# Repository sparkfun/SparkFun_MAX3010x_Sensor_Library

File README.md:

SparkFun MAX301x Particle Sensor Library
===========================================================

[*SparkFun Reflectance, Particle, and Pulse Ox sensor - MAX30105 (SEN-14045)*](https://www.sparkfun.com/products/14045)

That's my heartbeat!

This is a breadboard friendly breakout board for the Maxim MAX30105 reflectance, particle, and pulse ox sensor.

This library should work with other MAX3010x sensors including the MAX30102, MAX30101, and MAX30100. 

Library written by Nathan Seidle ([SparkFun](http://www.sparkfun.com)) and Peter Jansen ([Open Sensing Lab](https://github.com/opensensinglab)).

Repository Contents
-------------------

* **/examples** - Example sketches for the library (.ino). Run these from the Arduino IDE. 
* **/src** - Source files for the library (.cpp, .h).
* **keywords.txt** - Keywords from this library that will be highlighted in the Arduino IDE. 
* **library.properties** - General library properties for the Arduino package manager. 

Documentation
--------------

* **[Installing an Arduino Library Guide](https://learn.sparkfun.com/tutorials/installing-an-arduino-library)** - Basic information on how to install an Arduino library.
* **[Product Repository (MAX30105)](https://github.com/sparkfun/MAX30105_Particle_Sensor_Breakout)** - Main repository (including hardware files) for the MAX30105 particle sensor breakout board.
* **[Product Repository (MAX30101)](https://github.com/sparkfun/SparkFun_Photodetector_Breakout_MAX30101_Qwiic)** - Main repository (including hardware files) for the SparkFun Photodetector (MAX30101) - Qwiic.
* **[Hookup Guide (MAX30105)](https://learn.sparkfun.com/tutorials/max30105-particle-and-pulse-ox-sensor-hookup-guide)** - Basic hookup guide for the MAX30105 Particle Sensor breakout board.
* **[Hookup Guide (MAX30101)](https://learn.sparkfun.com/tutorials/sparkfun-photodetector-max30101-hookup-guide)** - Basic hookup guide for the SparkFun Photodetector (MAX30101) - Qwiic.

License Information
-------------------

This product is _**open source**_! 

Various bits of the code have different licenses applied. Anything SparkFun wrote is beerware; if you see me (or any other SparkFun employee) at the local, and you've found our code helpful, please buy us a round! Anything Maxim wrote has its own license. Anything that was co-writing with Peter Jansen is BSD.

Please use, reuse, and modify these files as you see fit. Please maintain attribution to SparkFun Electronics and release anything derivative under the same license.

Distributed as-is; no warranty is given.

- Your friends at SparkFun.

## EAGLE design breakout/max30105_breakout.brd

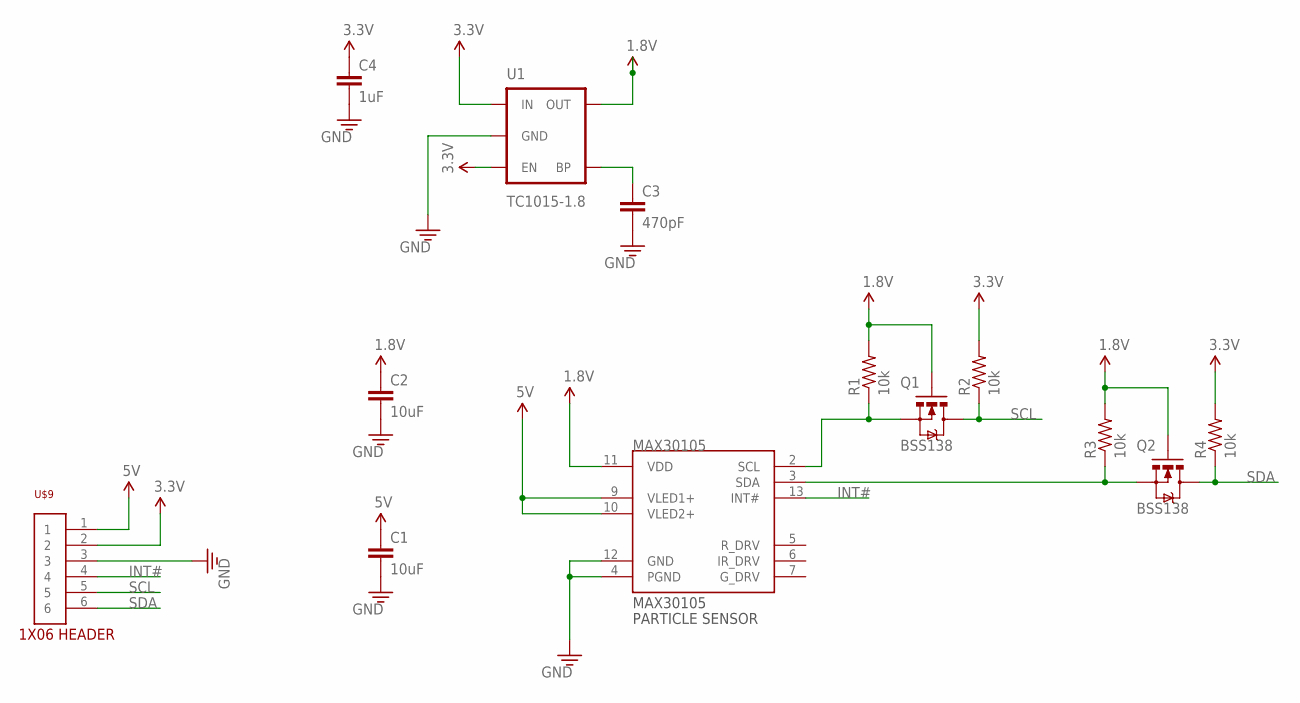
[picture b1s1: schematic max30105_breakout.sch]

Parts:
C1, C2: 10uF; 0805
C3: 470pF; 0603
C4: 1uF; 0603
MAX30105: MAX30105
Q1, Q2: BSS138; SOT23
R1, R2, R3, R4: 10k; 0603
U1: TC1015-1.8; SOT23-5
U$9: 1X06

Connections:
1.8V: C2.1, MAX30105.11 (VDD), Q1.1 (G), Q2.1 (G), R1.2, R3.2, U1.5 (OUT)
3.3V: C4.1, R2.2, R4.2, U1.1 (IN), U1.3 (EN), U$9.2
5V: C1.1, MAX30105.9 (VLED1+), MAX30105.10 (VLED2+), U$9.1
GND: C1.2, C2.2, C3.2, C4.2, MAX30105.4 (PGND), MAX30105.12 (GND), U1.2 (GND), U$9.3
INT#: MAX30105.13 (INT#), U$9.4
unnamed: MAX30105.2 (SCL), Q1.2 (S), R1.1
unnamed: C3.1, U1.4 (BP)
unnamed: MAX30105.3 (SDA), Q2.2 (S), R3.1
SCL: Q1.3 (D), R2.1, U$9.5
SDA: Q2.3 (D), R4.1, U$9.6

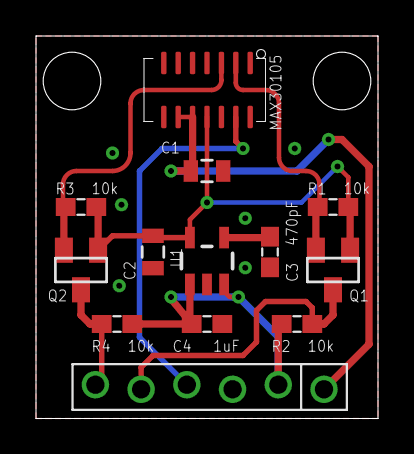
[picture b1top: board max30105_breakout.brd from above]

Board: 2 copper layers, 19.0 x 21.2 mm, 13 parts (0 on the bottom side), 10 nets.

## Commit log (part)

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2016-09-18 added breakout board schematics, board files, and renders
2016-09-18 Creating driver scaffold
2016-09-18 More scaffold -- added initial check for partID/revisionID
2016-09-18 Added die temperature reading
2016-09-18 Most of the basic configuration registers have been added, with the exception of the multiled configuration, and FIFO configuration. Data collection/FIFO reading is still TODO
2016-09-18 Added picture of breakout board
2016-09-22 Corrected register change bug. Added bit polling. Added tempF.
    All these are fairly small changes.
2016-09-22 Adding function to enable slots
2016-09-22 Implemented bitMask technique
    Simplified a bunch of functions.
2016-09-22 Added readData function
2016-09-23 Move config to library as 'defaultSetup'. Added FIFO WR/RW pointer checking.
    No major changes, just simplifcations and clean ups.
2016-09-23 Creating circular buffer for continual reading
    Works well. This is a really sensitive IC!
2016-09-23 Added 400kHz support. Defaults to 100kHz. Added Hz output.
2016-09-23 Added interrupt support
2016-09-23 Added proximity mode interrupt threshold
2016-09-24 Genericize to work with any I2C port, not just Wire.
    Needed for platforms like SAMDxx that have multiple I2C ports.
2016-09-25 Default to Wire if no port is provided.
2016-09-27 Fixed bug in SLOT defs. Reworked begin() to fit Arduino guide.
    Does not compile but there's too many things changing. Need to commit
    what's here.
2016-09-27 Moved data reading into library.
2016-09-28 Making ledMode control slot enabling
2016-10-03 Added example sketches. Moved files to match library structure.
2016-10-05 Small changes to heartrate example
2016-10-19 :tada: Added .gitattributes & .gitignore files
2016-10-20 Added adc control to setup(). Added PBA heart rate algorithm.
2016-10-20 Correcting typo
2016-10-20 Adding spo2 SPK algorithm and examples
2016-10-20 Adding heart beat example
2016-10-20 Small typo and white space fixes.
2016-11-16 Adding 3.3V note
2016-11-17 Fixing heartRate code to work on ESP
2016-11-17 Moved register defines to cpp. Changed to const static.
    Const static allows compiler to check for type conflicts.
2016-11-21 Splitting getRed() from getFIFORed() for better examples. When you call getRed() you now get the immediate environmental reading.
2016-11-21 Re-arranging examples
2016-11-21 Adding image to readme
2016-11-29 Rearrange examples
2016-11-30 Fixing directory structure
2016-11-30 Readme fix
2017-01-23 Adding support for SAM21 and other platforms
2017-01-27 Modifying Ex8 to work with SAMD21
2017-01-27 Updating version number
2017-09-03 Use correct separator in keywords.txt
    The Arduino IDE requires the use of a tab separator between the name and identifier. Without this tab the keyword is not highlighted.
    Reference: https://github.com/arduino/Arduino/wiki/Arduino-IDE-1.5:-Library-specification#keywords
2018-02-15 Fixing issue 4
2018-02-15 Rolling library version
2018-02-15 Capitalized Arduino.h. Fix issue 2 on breakout. Remove unused vars. Removed dup defines.
2018-02-15 Rolling lib ver
2018-03-03 Renamed FS to FreqS because there is an overlap with the FS library. Uncommented one line because it seems you had forgotten to do so.
2018-03-28 Fix for issue #12
2018-03-28 Rolling lib version
2018-04-03 Fix issue 14 - change sampleRate to int in example
2018-04-09 Adding example to demo 3200Hz reading for issue #2
2018-04-10 Roll lib ver
2018-06-08 Fix error in operator precedence
2018-06-08 Lib ver roll
2018-12-17 Sensor values mix up when using multiple sensors
    When using 2 (or more) sensors on the same device the sensor values read from the sensors can get mixed up.
    The struct sense is defined as a global and is reused from multiple instances of the MAX30105 class.
    Solution:
    Declare sense as class private:
2019-01-24 Change how we readTemperature(). Updated Temp Sense example.
    Fix for issue 19.
2019-12-27 Changed Begin function to prevent call to wire->begin (#1)
2019-12-27 changed library properties
2019-12-30 Changed Library properties. Added example to run MAX on EmotiBit.
2020-01-07 changed library properties to update name and URL. bumped version
2020-06-24 Update README.md
    Fix product repository link/desc
2020-06-25 Update README.md
    Add MAX30101 Product and Hookup Guide Links
2020-12-04 Basic Example (#2)
    * modified basic example to print data which can be seen in arduino plotter.
    * bumped lib version to 1.1.3
    * changes made as requested in Review.
    * Added readme as per review
    * Update ReadMe.md
    * minor print addition
2022-01-13 added async temp access
2022-01-13 minor changes to logging. added temp in F. tested working
2022-01-13 minor change
2022-05-25 Fix for #45
2022-08-26 Update MAX30105.h
    To avoid the issue of duplicate definition.

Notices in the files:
parts and their libraries:
arducorder-mini: Licensing: Creative Commons ShareAlike 4.0 International - https://creativecommons.org/licenses/by-sa/4.0
